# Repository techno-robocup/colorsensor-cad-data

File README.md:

# What does this repository do?

This repository contains the cad data for our color sensor we have used during 2024.

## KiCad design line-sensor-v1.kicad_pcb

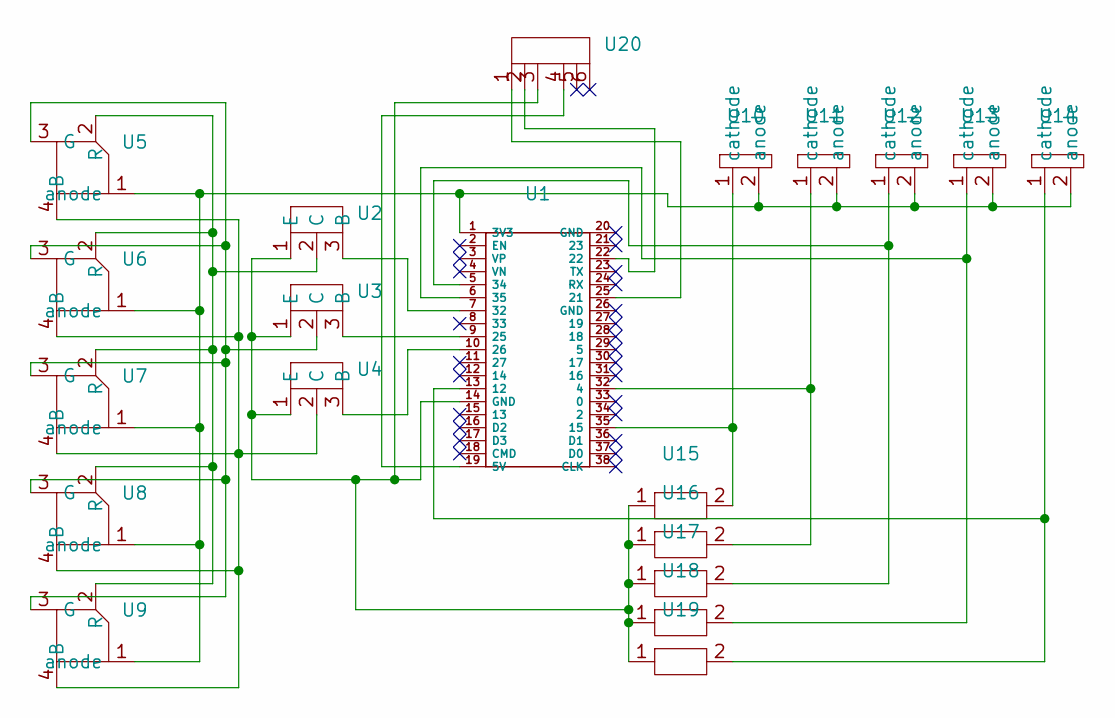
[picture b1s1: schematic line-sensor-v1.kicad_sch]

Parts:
U1: ESP32-DevKitC-32E
U2, U3, U4: トランジスタ
U5, U6, U7, U8, U9: OSTBMAZ2C1D-LED
U10, U11, U12, U13, U14: フォトトランジスタ
U15, U16, U17, U18, U19: resistance
U20: 6-pin

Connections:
unnamed: U1.1 (3V3), U5.1 (anode), U6.1 (anode), U7.1 (anode), U8.1 (anode), U9.1 (anode), U10.2 (anode), U11.2 (anode), U12.2 (anode), U13.2 (anode), U14.2 (anode)
unnamed: U1.32 (4), U11.1 (cathode), U16.2
unnamed: U1.19 (5V), U20.4
unnamed: U1.13 (12), U14.1 (cathode), U19.2
unnamed: U1.35 (15), U10.1 (cathode), U15.2
unnamed: U1.25 (21), U20.1
unnamed: U1.9 (25), U3.3 (B)
unnamed: U1.10 (26), U4.3 (B)
unnamed: U1.7 (32), U2.3 (B)
unnamed: U1.5 (34), U12.1 (cathode), U17.2
unnamed: U1.6 (35), U13.1 (cathode), U18.2
unnamed: U1.22, U20.2
unnamed: U2.2 (C), U5.2 (R), U6.2 (R), U7.2 (R), U8.2 (R), U9.2 (R)
unnamed: U1.14 (GND), U2.1 (E), U3.1 (E), U4.1 (E), U15.1, U16.1, U17.1, U18.1, U19.1, U20.3
unnamed: U3.2 (C), U5.3 (G), U6.3 (G), U7.3 (G), U8.3 (G), U9.3 (G)
unnamed: U4.2 (C), U5.4 (B), U6.4 (B), U7.4 (B), U8.4 (B), U9.4 (B)

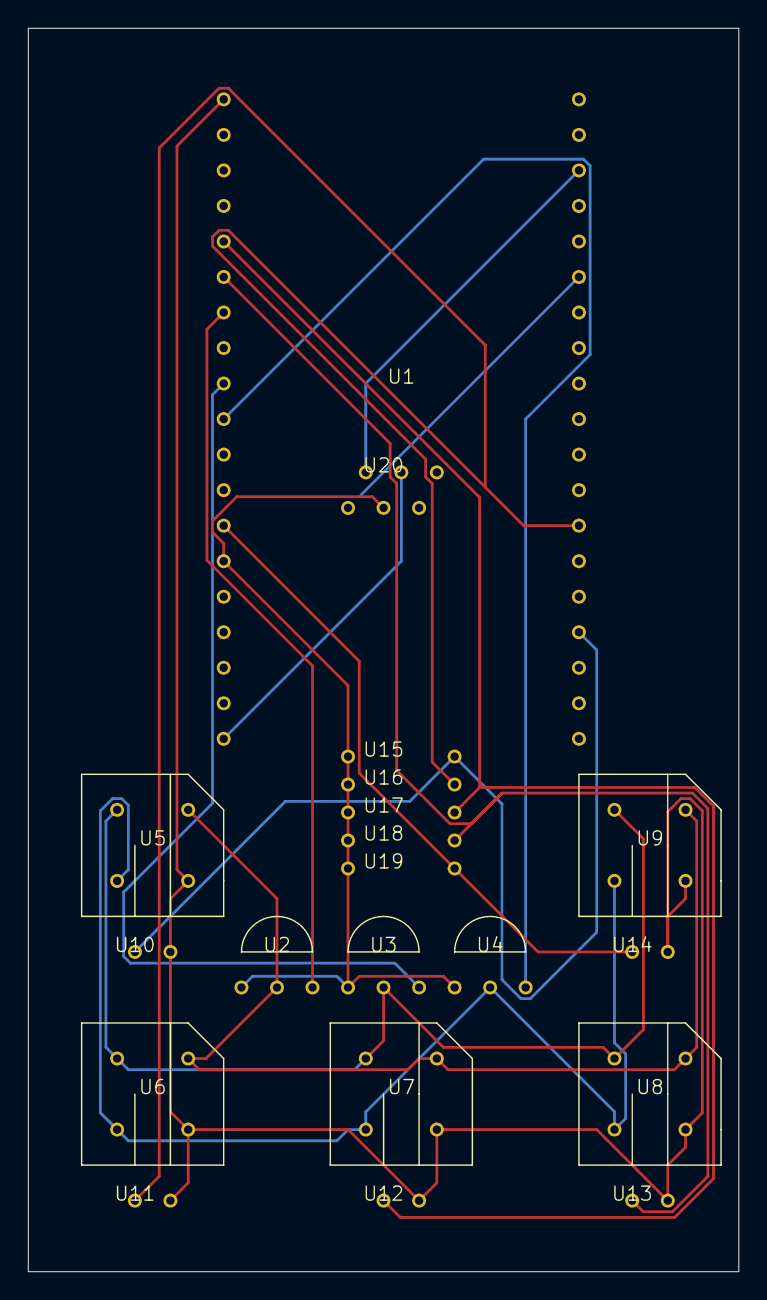
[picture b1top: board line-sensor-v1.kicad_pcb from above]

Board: 2 copper layers, 50.8 x 88.9 mm, 20 parts (0 on the bottom side), 16 nets.

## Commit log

2024-09-06 finished pcb
2025-05-23 Create LICENSE
2025-05-23 new: Created readme
2025-05-23 rm: Removed backup
